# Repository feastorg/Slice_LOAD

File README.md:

# Load Cell Amplifier Slice

Load Cell Amplifier Slice for BREAD.

## Introduction

[Short introduction on the project.]

## Usage

[Explain how to use the project. Include examples and screenshots if applicable.]

## Documentation

Please refer to the [docs](/docs) for more info.

---

<div align="center">
  
</div>

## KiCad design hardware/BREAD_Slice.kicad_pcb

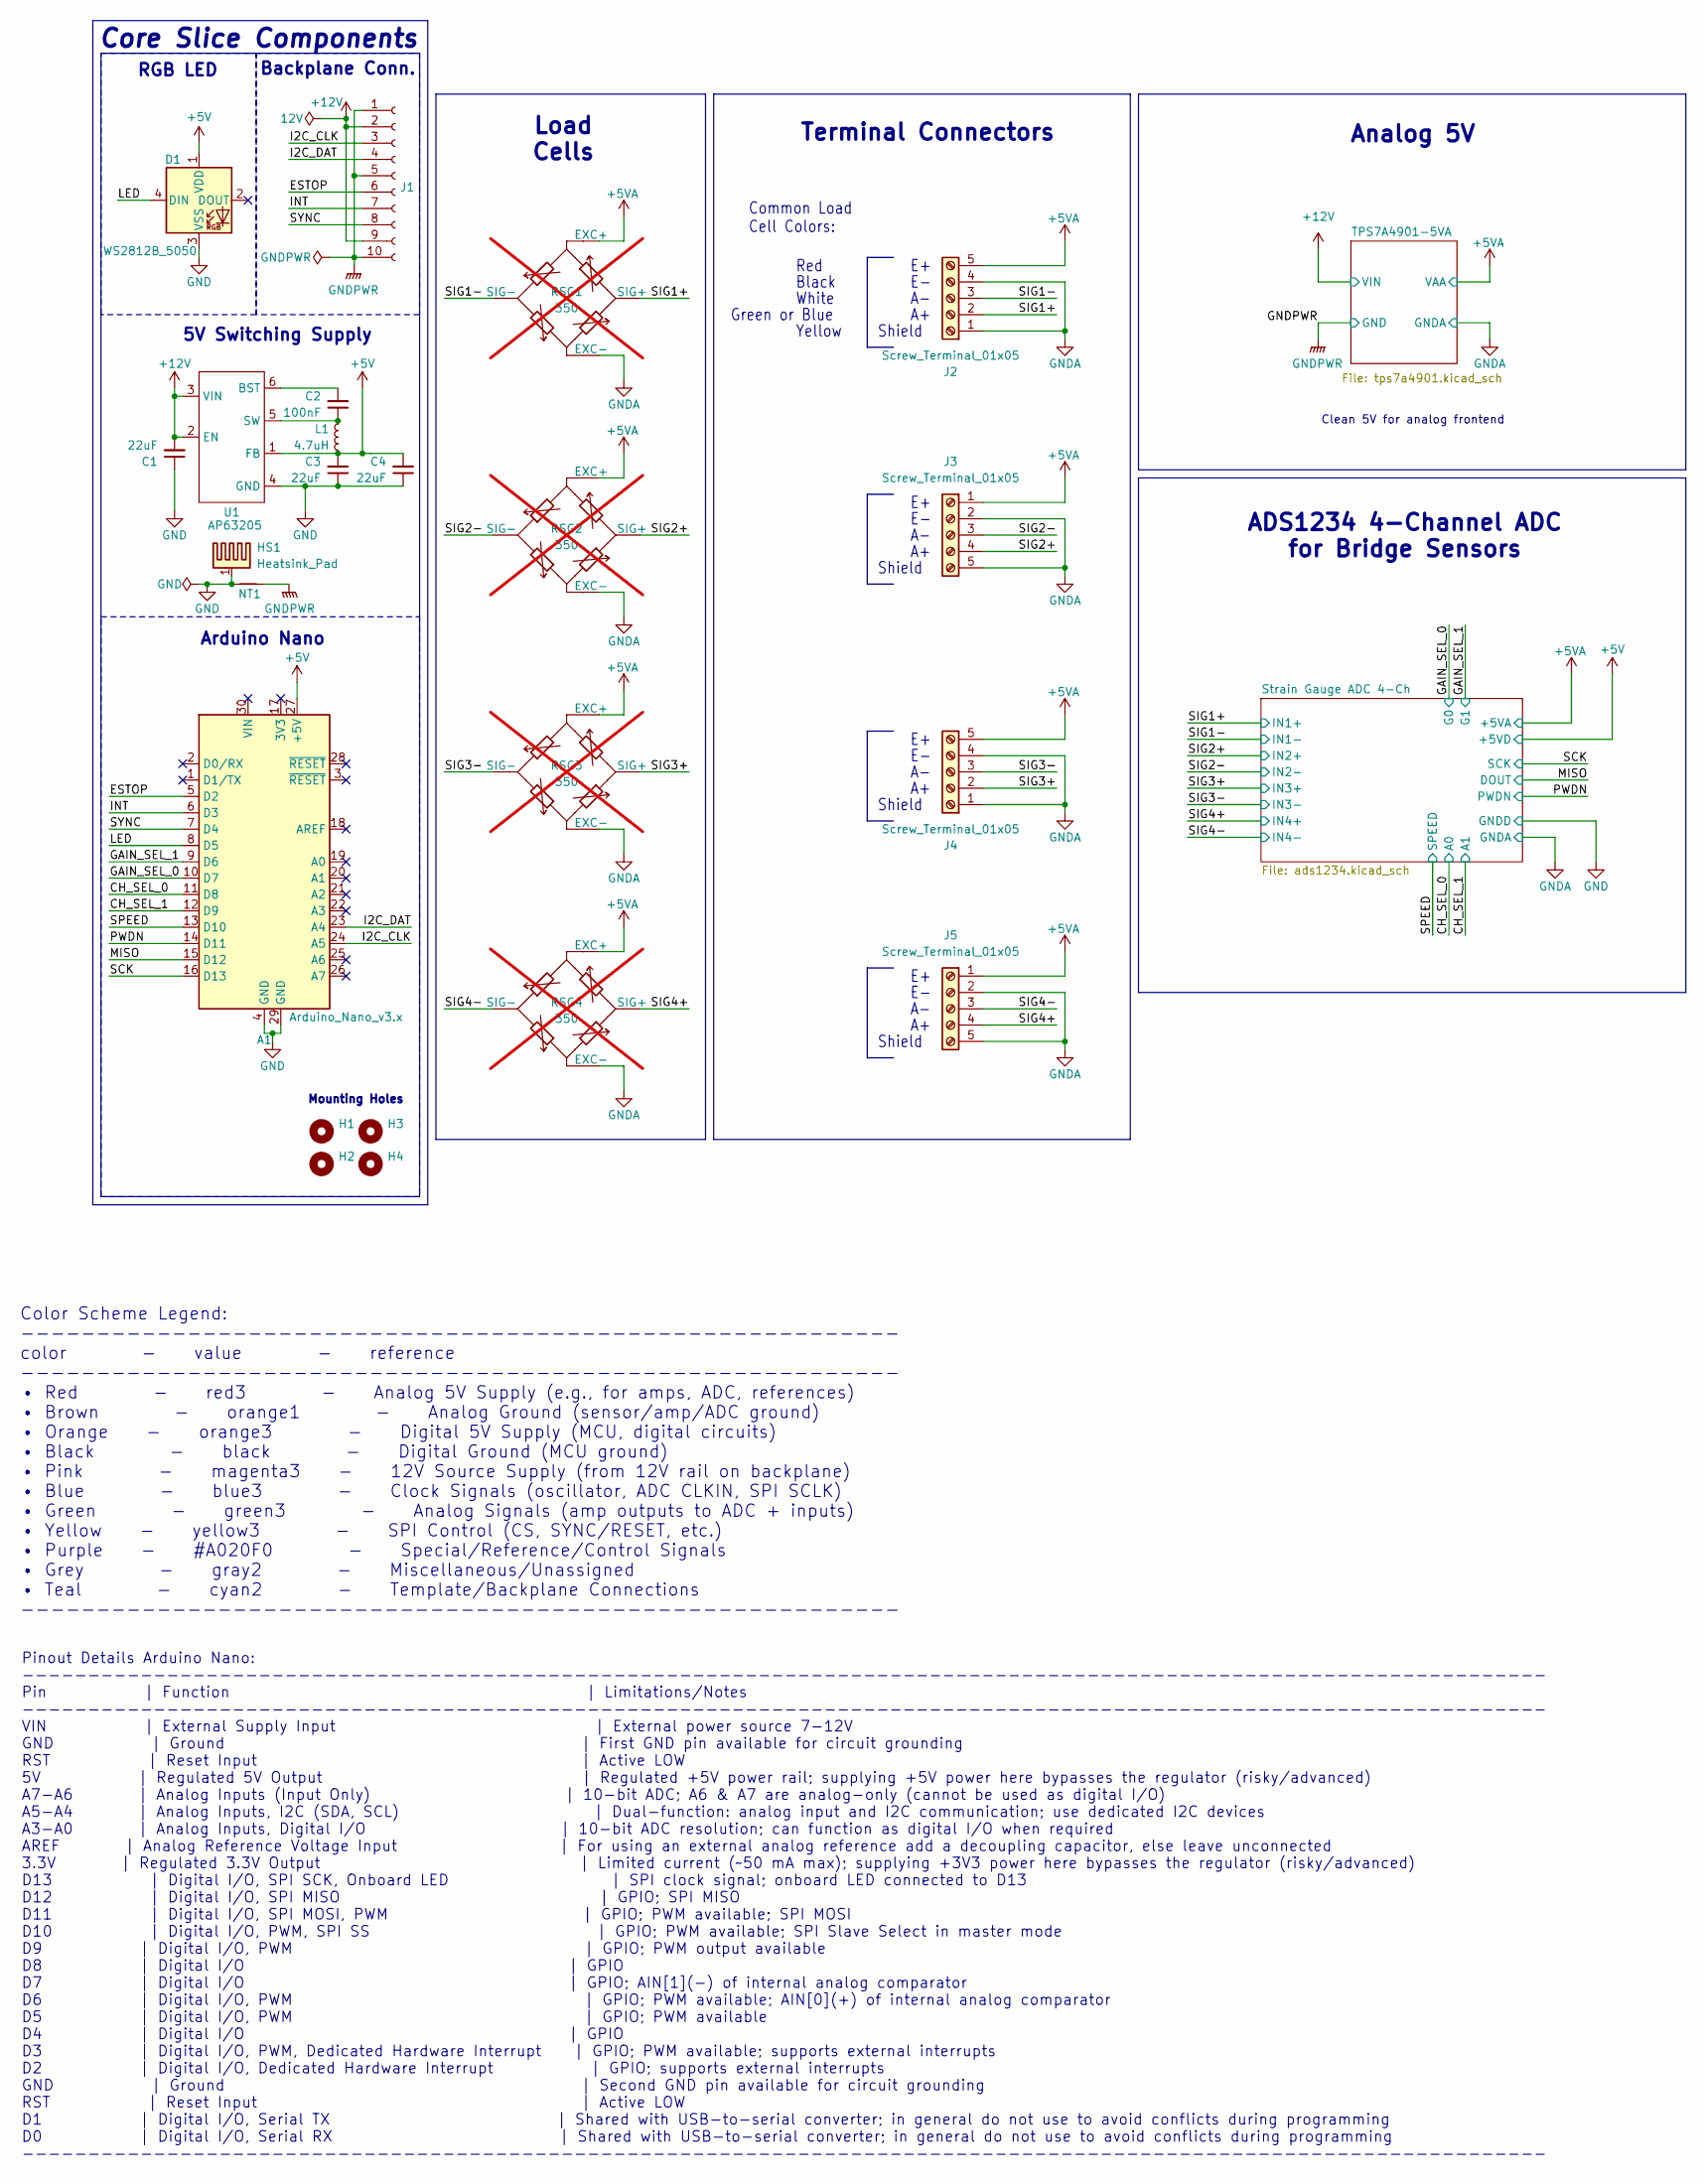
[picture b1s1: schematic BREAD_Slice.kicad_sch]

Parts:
A1: Arduino_Nano_v3.x; Arduino_Nano
C1, C3, C4: 22uF; C_1206_3216Metric
C2: 100nF; C_1206_3216Metric
D1: WS2812B_5050; WS2812-5050-4PIN
H1, H2, H3, H4: MountingHole; MountingHole_5mm
HS1: Heatsink_Pad; Thermal Pad
J1: Conn_01x10_Female; PinSocket_1x10_P2.54mm_Horizontal
J2, J3, J4, J5: Screw_Terminal_01x05; TerminalBlock_4Ucon_1x05_P3.50mm_Horizontal
L1: 4.7uH; L_1210_3225Metric
NT1: NetTie_2; NetTie-2_SMD_Pad2.0mm
RSG1, RSG2, RSG3, RSG4: 350; not fitted
U1: AP63205; TSOT-23-6

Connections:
+5V: A1.27 (+5V), C3.2, C4.2, D1.1 (VDD), L1.2, U1.1 (FB); also elsewhere on the board
+5VA: J2.5, J3.1, J4.5, J5.1, RSG1.1 (EXC+), RSG2.1 (EXC+), RSG3.1 (EXC+), RSG4.1 (EXC+); also elsewhere on the board
+12V: C1.2, J1.2, J1.9, U1.2 (EN), U1.3 (VIN); also elsewhere on the board
/CH_SEL_0: A1.11 (D8); also elsewhere on the board
/CH_SEL_1: A1.12 (D9); also elsewhere on the board
/ESTOP: A1.5 (D2), J1.6
/GAIN_SEL_0: A1.10 (D7); also elsewhere on the board
/GAIN_SEL_1: A1.9 (D6); also elsewhere on the board
/I2C_CLK: A1.24 (A5), J1.3
/I2C_DAT: A1.23 (A4), J1.4
/INT: A1.6 (D3), J1.7
/LED: A1.8 (D5), D1.4 (DIN)
/MISO: A1.15 (D12); also elsewhere on the board
/PWDN: A1.14 (D11); also elsewhere on the board
/SCK: A1.16 (D13); also elsewhere on the board
/SIG1+: J2.2, RSG1.3 (SIG+); also elsewhere on the board
/SIG1-: J2.3, RSG1.4 (SIG-); also elsewhere on the board
/SIG2+: J3.4, RSG2.3 (SIG+); also elsewhere on the board
/SIG2-: J3.3, RSG2.4 (SIG-); also elsewhere on the board
/SIG3+: J4.2, RSG3.3 (SIG+); also elsewhere on the board
/SIG3-: J4.3, RSG3.4 (SIG-); also elsewhere on the board
/SIG4+: J5.4, RSG4.3 (SIG+); also elsewhere on the board
/SIG4-: J5.3, RSG4.4 (SIG-); also elsewhere on the board
/SPEED: A1.13 (D10); also elsewhere on the board
/SYNC: A1.7 (D4), J1.8
GND: A1.4 (GND), A1.29 (GND), C1.1, C3.1, C4.1, D1.3 (VSS), HS1.1, NT1.1, U1.4 (GND); also elsewhere on the board
GNDA: J2.1, J2.4, J3.2, J3.5, J4.1, J4.4, J5.2, J5.5, RSG1.2 (EXC-), RSG2.2 (EXC-), RSG3.2 (EXC-), RSG4.2 (EXC-); also elsewhere on the board
GNDPWR: J1.1, J1.5, J1.10, NT1.2; also elsewhere on the board
unnamed: C2.2, U1.6 (BST)
unnamed: C2.1, L1.1, U1.5 (SW)

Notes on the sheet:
5V Switching Supply
Red
Shield
Common Load Cell Colors:
Analog 5V
Pinout Details Arduino Nano: -------------------------------------------------------------------------------------------------------------------- Pin | Function | Limitations/Notes -------------------------------------------------------------------------------------------------------------------- V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
RGB LED
White
Color Scheme Legend: ---------------------------------------------------------- color - value - reference ---------------------------------------------------------- • Red - red3 - Analog 5V Supply (e.g., for amps, ADC, references) • Brown - orange1 - Analog Ground (sensor/amp/ADC ground) • Orange -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
Green or Blue
Yellow
Terminal Connectors
Black
Core Slice Components
ADS1234 4-Channel ADC for Bridge Sensors
Arduino Nano
Clean 5V for analog frontend
Mounting Holes
Backplane Conn.
Load Cells

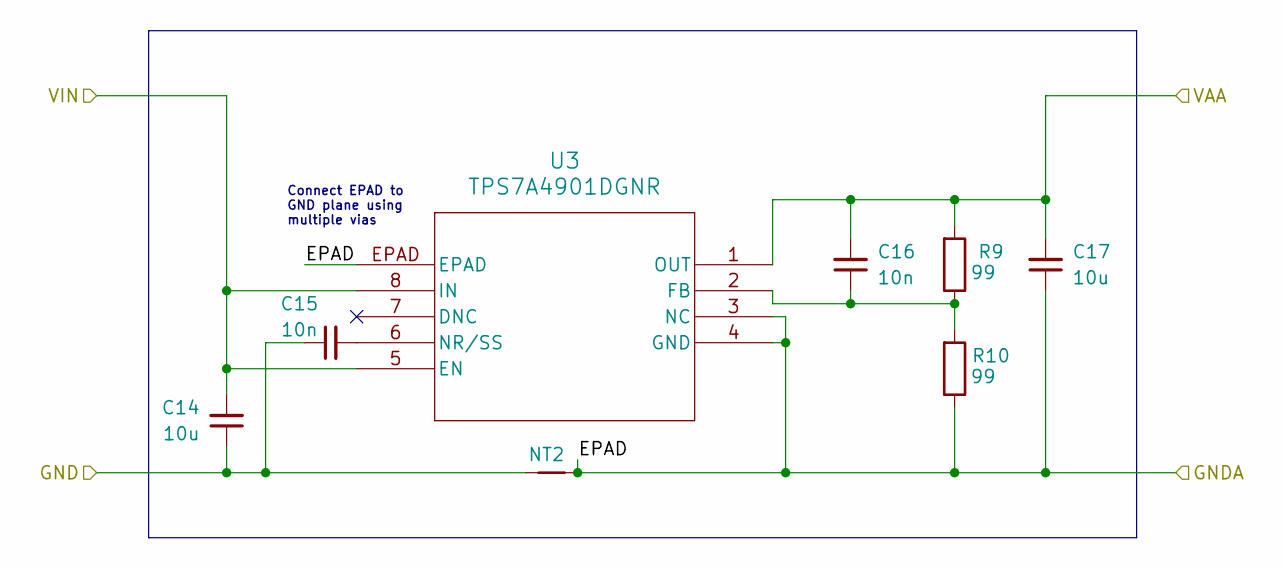
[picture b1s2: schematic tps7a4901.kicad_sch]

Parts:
C14, C17: 10u; C_0805_2012Metric_Pad1.18x1.45mm_HandSolder
C15, C16: 10n; C_0805_2012Metric_Pad1.18x1.45mm_HandSolder
NT2: NetTie_2; NetTie-2_SMD_Pad2.0mm
R9, R10: 99; R_0805_2012Metric_Pad1.20x1.40mm_HandSolder
U3: TPS7A4901DGNR; DGN8_1P89X1P57

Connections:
+5VA: C16.2, C17.2, R9.2, U3.1 (OUT); also elsewhere on the board
+12V: C14.2, U3.5 (EN), U3.8 (IN); also elsewhere on the board
GNDA: C17.1, NT2.2, R10.1, U3.3 (NC), U3.4 (GND), U3.EPAD; also elsewhere on the board
GNDPWR: C14.1, C15.1, NT2.1; also elsewhere on the board
unnamed: C16.1, R9.1, R10.2, U3.2 (FB)
unnamed: C15.2, U3.6 (NR/SS)

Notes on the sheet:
Connect EPAD to GND plane using multiple vias

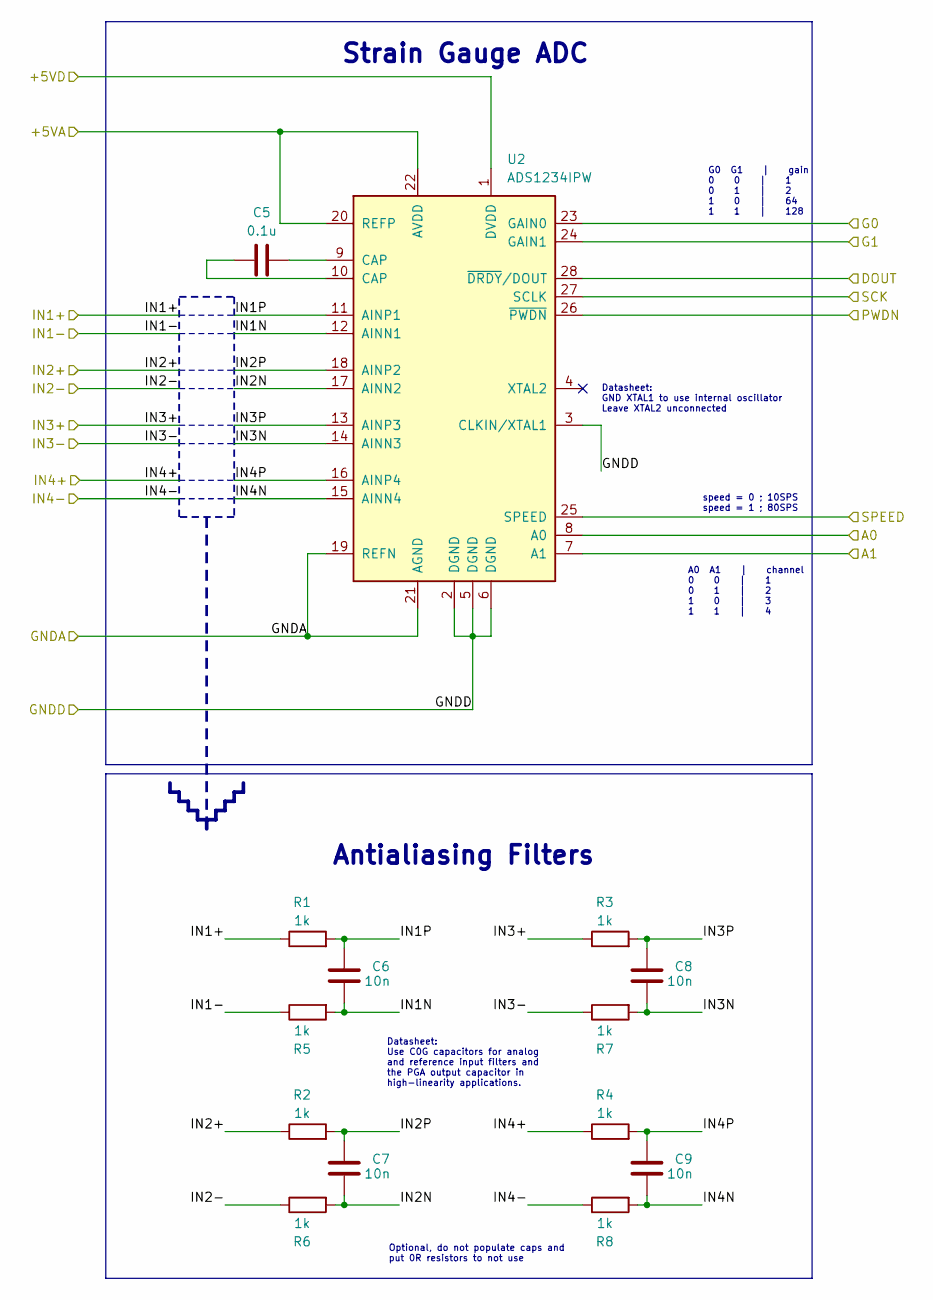
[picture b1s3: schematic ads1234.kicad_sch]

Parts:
C5: 0.1u; C_0603_1608Metric_Pad1.08x0.95mm_HandSolder
C6, C7, C8, C9: 10n; C_0603_1608Metric_Pad1.08x0.95mm_HandSolder
R1, R2, R3, R4, R5, R6, R7, R8: 1k; R_0603_1608Metric_Pad0.98x0.95mm_HandSolder
U2: ADS1234IPW; TSSOP-28_4.4x9.7mm_P0.65mm

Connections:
+5V: U2.1 (DVDD); also elsewhere on the board
+5VA: U2.20 (REFP), U2.22 (AVDD); also elsewhere on the board
/CH_SEL_0: U2.8 (A0); also elsewhere on the board
/CH_SEL_1: U2.7 (A1); also elsewhere on the board
/GAIN_SEL_0: U2.23 (GAIN0); also elsewhere on the board
/GAIN_SEL_1: U2.24 (GAIN1); also elsewhere on the board
/MISO: U2.28 (~DRDY/DOUT); also elsewhere on the board
/PWDN: U2.26 (~PWDN); also elsewhere on the board
/SCK: U2.27 (SCLK); also elsewhere on the board
/SIG1+: R1.1; also elsewhere on the board
/SIG1-: R5.1; also elsewhere on the board
/SIG2+: R2.1; also elsewhere on the board
/SIG2-: R6.1; also elsewhere on the board
/SIG3+: R3.1; also elsewhere on the board
/SIG3-: R7.1; also elsewhere on the board
/SIG4+: R4.1; also elsewhere on the board
/SIG4-: R8.1; also elsewhere on the board
/SPEED: U2.25 (SPEED); also elsewhere on the board
/Strain Gauge ADC 4-Ch/IN1N: C6.1, R5.2, U2.12 (AINN1)
/Strain Gauge ADC 4-Ch/IN1P: C6.2, R1.2, U2.11 (AINP1)
/Strain Gauge ADC 4-Ch/IN2N: C7.1, R6.2, U2.17 (AINN2)
/Strain Gauge ADC 4-Ch/IN2P: C7.2, R2.2, U2.18 (AINP2)
/Strain Gauge ADC 4-Ch/IN3N: C8.1, R7.2, U2.14 (AINN3)
/Strain Gauge ADC 4-Ch/IN3P: C8.2, R3.2, U2.13 (AINP3)
/Strain Gauge ADC 4-Ch/IN4N: C9.1, R8.2, U2.15 (AINN4)
/Strain Gauge ADC 4-Ch/IN4P: C9.2, R4.2, U2.16 (AINP4)
GND: U2.2 (DGND), U2.3 (CLKIN/XTAL1), U2.5 (DGND), U2.6 (DGND); also elsewhere on the board
GNDA: U2.19 (REFN), U2.21 (AGND); also elsewhere on the board
unnamed: C5.1, U2.10 (CAP)
unnamed: C5.2, U2.9 (CAP)

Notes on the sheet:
Optional, do not populate caps and put 0R resistors to not use
Datasheet: GND XTAL1 to use internal oscillator Leave XTAL2 unconnected
A0 A1 | channel 0 0 | 1 0 1 | 2 1 0 | 3 1 1 | 4
Antialiasing Filters
Datasheet: Use C0G capacitors for analog and reference input filters and the PGA output capacitor in high-linearity applications.
Strain Gauge ADC
G0 G1 | gain 0 0 | 1 0 1 | 2 1 0 | 64 1 1 | 128
speed = 0 ; 10SPS speed = 1 ; 80SPS

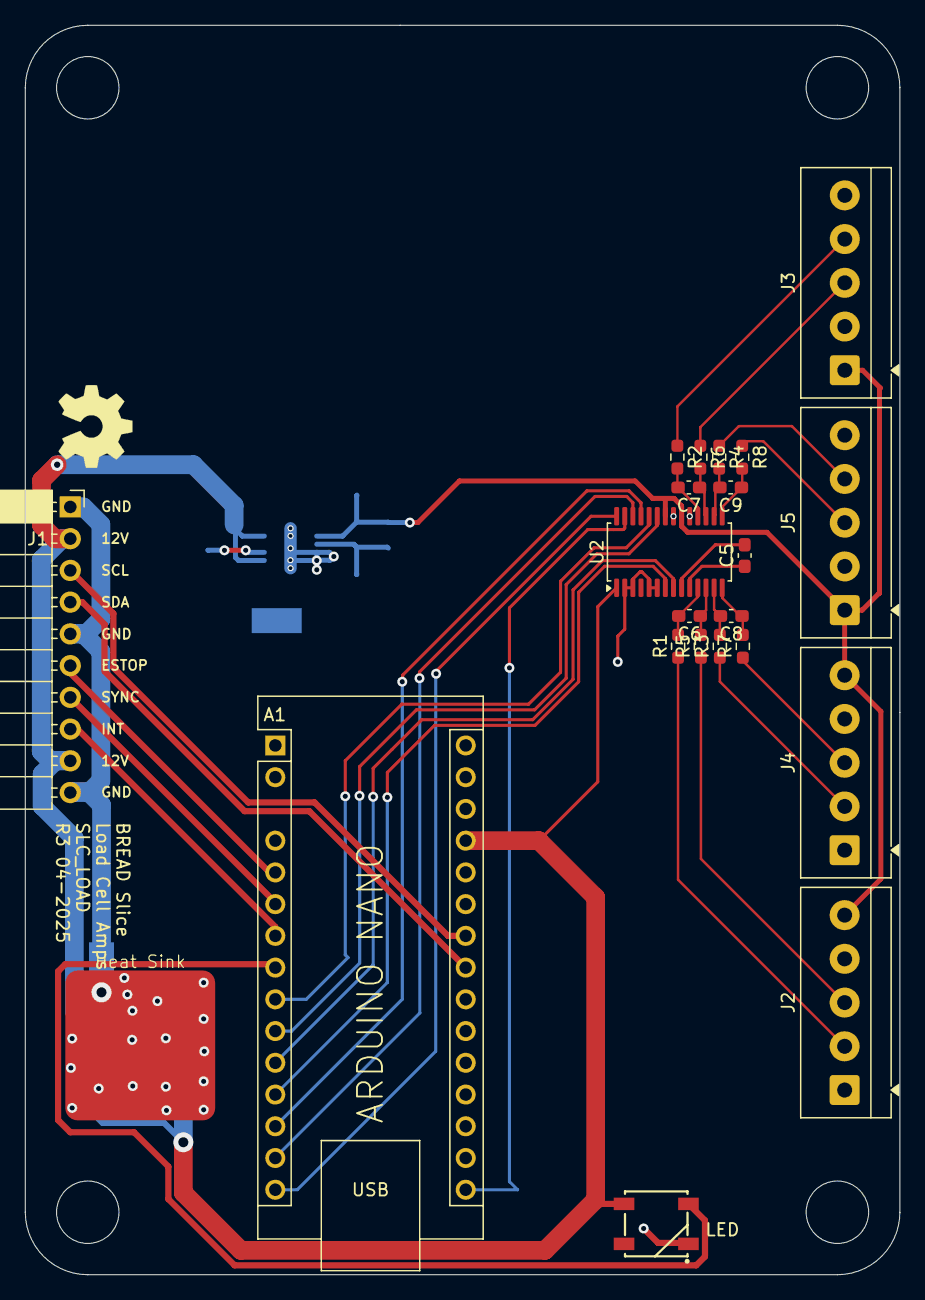
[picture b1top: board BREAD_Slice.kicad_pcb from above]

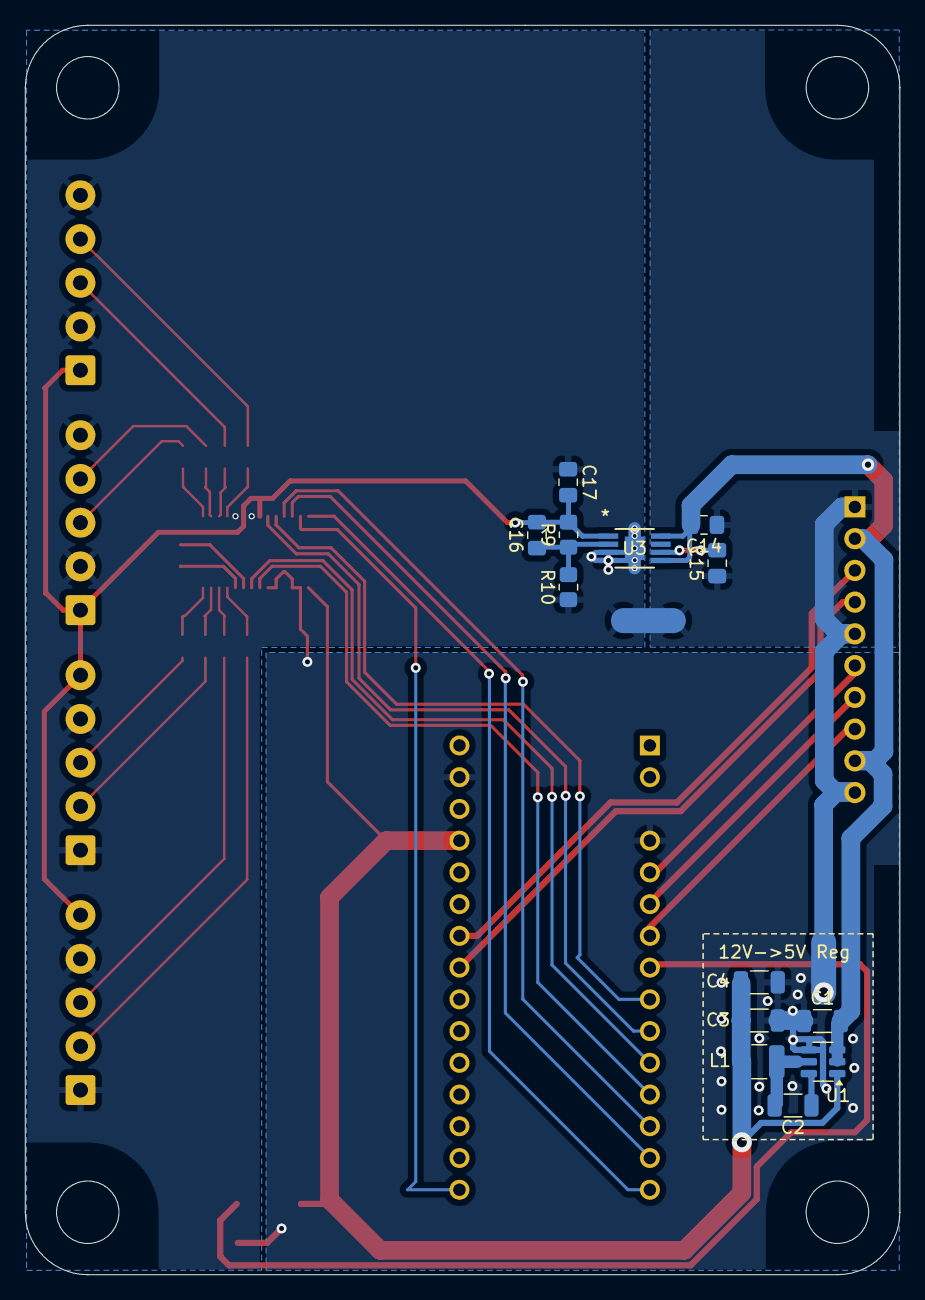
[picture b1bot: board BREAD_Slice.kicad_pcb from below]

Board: 2 copper layers, 70.0 x 100.0 mm, 42 parts (15 on the bottom side), 42 nets.

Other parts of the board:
Logo1: Logo_Open_Hardware_Small; OSHW-Symbol_6.7x6mm_SilkScreen

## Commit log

2024-09-10 set repo
2025-04-08 finished first pass of schematic and board
2025-04-10 added tps analysis
2025-04-19 minor tweaks
2026-04-18 chore: minor updates
2026-05-20 Add slice.yaml manifest (schema v1.0)
2026-05-24 Add KiBot/docs pipeline
2026-05-24 Update TODO with CI findings
2026-05-24 Standardize TODO.md with Pass 1/Pass 2 structure
